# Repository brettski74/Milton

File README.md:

# Milton - The Makeshift Melt Master!

Milton is a web interface and set of utilities for controlling a solder reflow hotplate connected to various power supplies. Currently it supports bench power supplies with SCPI or Modbus support with plans to add support for other options as time, resources and information allow.

Join us on [Discord](https://discord.gg/dnQJEGFCZ9) to meet other people interested in DIY solder reflow hotplates, ask questions, make suggestions or discuss problems. You can also raise issues here and I'll take a look when I can.

Milton requires some playing around to set up and configure currently. Installation packages for Debian, Arch and a bare tarball installation should be coming soon.

## Features

* Bootstrappable - no need to hand-solder SMD components before you have a working reflow soldering solution.
* Support for SCPI and Modbus based power supplies.
* Web interface for ease of use and pretty graphs!
* Command line interface if a graphical UI is not your thing or not practical or you need to automate as part of a larger workflow.
* Real temperature control with various control algorithms available (bang-bang, feed-forward, PI and hybrid).
* Real temperature measurement without the need for an explicit temperature sensor.
* Temperature prediction models to provide noise reduction for control and to allow estimating the average temperature across your hotplate rather than for a single point that may or may not be representative of your load.
* Includes reflow profiles for tin-bismuth (SnBi) and tin-lead (SnPb) solder alloys based on JEDEC recommendations.
* Calibration via external temperature sensors if necessary to recalibrate the models for different hotplate assemblies.

## Requirements

* Linux computer with USB or RS-232 serial communications capabilities. This could include single board computers like a Raspberry PI or others.
* A variable DC power supply that supports remote control via RS-232 or USB-serial communications.
* SCPI or Modbus protocol support in your power supply.
* Perl 5 (see dependencies below)
* A [hotplate](#where-to-get-your-hotplate)

Note that power requirements depend on a lot. As a general rule, a 100mm x 100mm will need a power supply capable of 90W or more. 150W is desirable, but 90W can work reasonably well although may be a little slower - especially with heavier loads.

You will also need to match the resistance of your hotplate with your power supply. Your hotplate is basically just a copper resistor. It will dissipate whatever power you can put into it, but if the resistance is too high for your power supply's voltage capabilities or too low for it current capabilities, then you won't be able to utilize the full power output of your supply. Note that the resistance of your hotplate will increase with temperature and you generally want the highest power output at the top end of your reflow cycle. The resistance your most care about will be the resistance of the hotplate when its at your peak reflow temperature (around 220 celsius for tin-lead solder) rather than the value you measure at room temperature.

## Installation

Milton releases will come as a tarball that can be installed either as a user local installation, or as a global shared installation that can be used by multiple users. One reasons you might want to do this is if you have multiple hotplates connected to a host. One simple way of handling this is to simply run a separate instance under separate users, each with their own configuration.

You can also install the latest source by cloning the git repo and running the installation from your cloned sources. While this is the only option currently, once release tarballs start becoming available, those should be the preferred source of your installation. Release tarballs should be relatively bug free, working releases that are stable and reliable. The git repo will contain the latest code, but may include bugs and other issues from time to time.

Installation process is mostly the same. For the tarball releases, you must first extract the contents of the tarball:

```
xz -dc milton-<version>.tar.xz | tar xv
```

Now chdir to the base directory of your release (or git repo). For example:

```
cd milton-<version>
```

You should see a file called install.sh in your current directory. Run it using:

```
./install.sh
```

It should prompt your for a few things. If you are doing a global shared installation and/or using your system package manager to install perl dependencies, you may need to provide your password for sudo. If you don't trust me enough to let the installation script run sudo, then do a user local installation and use cpan or cpanm for installating your perl dependencies and it shouldn't be required. Alternatively, you can manually install all the perl dependencies and setup the required directories prior to running the installation.

The installation should get you close to a working installation, however, after installation you will still need to take care of the following tasks manually:

1. Add $MILTON_BASE/bin to your PATH environment variable.
1. Configure Milton for your power supply.
1. Calibrate your system.

### Configuring Milton

The `mledit` script can be used for editing Milton configuration files. If no filenames are specified on the command line, then it assumes you want to edit the main psc.yaml file. Filenames should be relative to the Milton configuration search path, such as controller/hybrid-pi.yaml. mledit does the following things automatically for you:

1. Find the configuration file in the Milton configuration search path.
1. If the file being edited is in the shared configuration directory, it first makes a copy in your user configuration directory and edits that.
1. Test load the file on exit to verify that it can be loaded without issue and warns you if errors are detected.

In addition to configuration basic operation of Milton, which should mostly be handled during the installation process, you will also need to [calibrate milton](CALIBRATION.md) for your particular hotplate.

## Using Milton

Before using Milton to do any real work like reflowing PCBs or testing heat sink assemblies, you will probably need to [calibrate Milton](CALIBRATION.md). Your results may vary without proper calibration of at least the RTD temperature-resistance mapping.

The command line interface uses the script `psc` to run commands. You can probably run something like:

```
psc reflow
```

to run a reflow cycle using the default reflow profile.

OR 

```
psc power --duration 900 60
```

to run the hotplate at a constant power level of 60W for 900 seconds.

TODO: Document more of the command-line options.

The web interface can be started with the command:

```
milton daemon
```

Milton is a mojolicious application that provides a web-based front end that wraps the command-line interface, so whether you run the `psc` directly or use the web interface, you're using the same code. I hope that the web interface is mostly self-explanatory, but for more advanced topics like calibration, documentation is a work in progress... or more realistically a work to be in progress. :)

### Temperature Measurement

Most temperature controlled systems use a heating element, burner or heat pump and a separate temperature sensor device. There are a lot of advantages to doing this, however some heating elements can also be used as a temperature sensor - with some caveats. This is how Milton currently works. The resistance of copper changes with temperature in a predictable and known way. In fact, this property of copper is sometimes used in a type of real, commercial/industrial temperature sensor called an RTD (Resistance Temperature Detector). These are just temperature dependent resistors made from metals such as copper or other metals/alloys with suitable properties. The copper trace on a PCB can be used as a heating element if made long and thin. If we know the resistance of the copper trace at one or more temperatures, then we can measure it's resistance to determine what its current temperature us.

Milton powers the heating element using a variable DC power supply that can be controlled via some communications interface. Currently, Milton supports SCPI and Modbus communciations over RS-232 or USB serial connections. Using this, we can read the output voltage and current. This allows us to calculate the resistance using Ohm's law. Note that there are some slight errors in these measurements due to things like lead and contact resistance, but these are negligible compared to the magnitude of the heating element resistance. They're also mostly taken care of during calibration. If we know the current temperature and the resistance of the heating element, we can use this to vary the supply voltage to send the right amount of power to get the hotplate temperature where we want it.

### Temperature Prediction

One of the drawbacks of using the heating element trace as both a heating element and a temperature sensor is that the heating element has low thermal mass and tends to vary more widely than the hotplate surface or the load on the hotplate (ie. your PCB to be reflowed). Using the heating element temperature reading directly is problematic and may be difficult to control - particularly if you're using an FR4 PCB as your hotplate. Prediction models allow us to use the measured heating element temperatures to predict what the hotplate surface temperature will be given the historical heating element temperature measurements that we've taken. With proper calibration, these models can be surprisingly accurate. The calibration provided in the release should work well for aluminimum PCBs that are assembled in a similar manner to the ones I have built. If this calibration is not working well for your particular assembly, Milton provides ways to re-calibrate the model to better reflect how your hotplate behaves.

It's also worth noting that loading the hotplate does change it's thermal behaviour.Testing so far has shown that this difference is not significant for the purpose of doing reliable solder reflow - at least with the hotplate assemblies described in this project. Feel free to experiment with new designs and let me know what you find!

If the release calibration is not working at all for you, the base predictor class - Milton::Predictor - does provide a pass-through predictor that simply gives the heating element temperature as the predicted hotplate temperature. For aluminium hotplate PCBs, this may work well enough to get you going until you can do your own calibration of the prediction model. For FR4 hotplate PCBs, this is probably not an option but if you're still using an FR4 hotplate, I highly recommend that you upgrade to aluminium. They seem to be superior in just about every way.

### Temperature Control

The control algorithms vary in their precision, need for calibration and sensitivity to mis-calibration. All of them rely on a properly calibrated temperature prediction model. Without good temperature prediction, you cannot hope to do good control. Note that raw measurements are often noisy which complicates control. You want a good prediction model for the noise filtering it provides.

There are three main control strategies currently available in Milton.

Bang-Bang control is the simplest. This works similar to the stove and oven in your kitchen. If the temperature is too low, we turn the heating element on. If the temperature is too high, we turn the heating element off - or something closely approximating off. Note that Milton always needs some current flowing through the heating element in order to measure its temperature, so the off state is really just a minimum power state. Bang-Bang control does support asymetric hysteresis, so you can specify how far above the temperature set-point the hotplate must be to turn off and how far below the temperature set-point the hotplate must be to turn on. This control strategy requires no calibration - other than a working temperature prediction model. It doesn't produce the smoothest temperature response but rather tends to oscillate around the temperature set-point by a few degrees celsius. It may also provide greater thermal and mechanical stress to your hotplate than other models due to the extreme on-off power levels that it sends into your hotplate. That said, I have not yet seen any appreciable deterioration in my aluminium hotplates after hundreds of reflow cycles and for a while this was the only control scheme I considered necessary. The results are more than adequate for solder reflow.

PI control (or PID as you may have heard it called) is a closed-loop feedback control scheme that measures the error between the desired temperature and the measured (or predicted temperature in our case) and uses that to detemine the control signal (ie. how much power to send to the hotplate) required to correct that error. The PID acronym comes from *Proportional*, *Integral* and *Differential* gains that the controller uses to produce the control signal. The proportional gain is applied to the error directly. The integral gain is applied to the integral of the error over time. The differential gain is applied to the derivative of the error over time. These three values are added together to produce the control output (ie. desired power level for the hotplate in our case). Thermal systems rarely need the differential gain or if they do use it, it's generally very small and often requires filtering of the derivative to avoid noise causing controllability problems. In our case, we simply ignore the differential term, so we really just have a PI controller with proportional and integral gains. These gains are adjustable parameters that may require some calibration, although there is a fairly wide range of values that will work reasonably well for any given hotplate. There are algorithms for calibrating these parameters - such as the well-known Ziegler-Nichols method, which Milton does not currently implement. Milton does have a calibration routine for the PI gains based on temperature prediction and a least-squared-error optimization, but the results so far were not impressive and so far the results with educated guesses have been better than what the optimization provided. The proportional gain generally gets the control into the ballpark, but with some offset error. The integral gain slowly corrects for this offset error, which brings the system closer to the desired state over time. PI controllers are good at adjusting to changing environmental conditions (eg. a load on the hotplate) but can also be prone to overshoot or undershoot when there are control changes required (eg. different rates of heating required). Proper selection of the gain values can improve this.

Feed-forward control requires a model for how the system responds to control inputs and then uses this model to estimate how much power is required to get from the current system state to the desired system state. It is the most sensitive to miscalibration, but when well-calibrated can often produce the smoothest, over/undershoot free temperature response you're likely to see. The downside is that feed-forward control is not great at adjusting for changes in environmental conditions like the PI controller. Feed-forward will generate higher power output commands in response to a load on the hotplate, but is unable to correct for the offset error that results. For most practical loads, this offset error is unlikely to be large enough to prevent reliable reflow, but a PCB loaded with components with high thermal mass may produce lower temperatures and/or require longer dwell time. This is why the feed-forward controller is implemented as a hybrid controller with the PI controller - HybridPI - so you can combine the best of both worlds. 

## Building Milton

TODO

## Where To Get Your Hotplate?

In theory, virtually any hotplate with a copper heating element should work but it was designed with PCB hotplates in mind. There are some example layouts for aluminium PCBs available in the [resources](resources) directory. You can also roll your own or get help from [Emmett](https://github.com/brettski74/Emmett) to build one to meet your needs.

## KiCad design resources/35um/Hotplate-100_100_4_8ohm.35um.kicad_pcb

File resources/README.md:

# Milton Resources

Here you'll find a collection of resources for setting up hotplates and other hardware to work with Milton.

## Safety

You'll probably see safety mentioned more than once in this repo. A reflow hotplate is a potentially
dangerous device that could cause serious burns or pose a fire hazard if not built, maintained and used
carefully. Commercial devices in many markets are required to go through extensive testing to ensure that
they are inherently safe and mitigate most of the common fire and burn hazards. I am not an expert. I'm
just a guy on the internet giving you my best opinions about how I think you can mitigate some of these
risks. Ultimately, if you choose to build a solder reflow hotplate using mine or anyone else's designs,
you understand that you are responsible for ensuring that the device that you build is safe and operated
safely. While I have included advice on how I think some of these risks can be mitigated, it is entirely
possible that you follow everything I say to perfection and you could still burn yourself, others or your
house.

### Thermal Fuse

The thermal fuse is a soldered link incorporated into the heating element circuit that must be in place
for the heating element to work. Pay close attention to the setup instructions that describe how to set
up the thermal fuse if you want it to work reliably. The type of solder used as well as the size and
geometry of the link and the pads on which it is mounted factor into how reliably it *trips* at the
expected temperature. Under normal use, this component should never make a difference, but in the event of
a thermal fault, it provides a last line of defence that will prevent the hotplate from continuing to heat
past a useful limit. If set up well, the link should drop at or below about 240°C. An incorrectly set up
thermal fuse link may stay connected well above 280°C or higher. There are some common household materials
that can ignite at these temperatures.

### Power Connections

The recommended method of connecting power to the board involves using solid copper wire and screw terminals
to securely clamp the wire in place. Solid copper wire is used for its rigidity. In the event of a thermal
fault, the hotplate could potentially get hot enough to reflow the power connection solder joints. If floppy,
flexible wires have been used, these wires may drop away from the board and fall... who knows where? The
intention of using solid copper wire is that they are bent into shape so the wires are under neglible stress
and the screw terminals hold them firmly in place so that if the power connections reflow, the power connection
wires stay put and don't inadvertently fall onto anything which might create a hazard or other problem.

You may get the idea that the power connections themselves could be used as a safety device and disconnect
power during a thermal fault, however, this is not recommended for at least the following reasons.

1. Copper doesn't make a good spring and even if you can create sufficient strain in the wires during setup
to make them spring away to a safe position if the joints reflow, copper does not retain that strain well
and it will relax over the kinds of temperatures that the power connections may be exposed to. After some
number of reflow cycles, that strain may be all but gone and then the wires won't move much or at all in a
subsequent thermal fault.
1. Materials that are good at being springs and are likely to retain that springiness as the hotplate goes
through many reflow cycles (eg. Phosphor Bronze) have other challenges such as poor electrical conductivity
and poor solderability due to surface oxidation that may make them difficult to form high quality joints
with the hotplate PCB.
1. Even with a good spring material like phosphor bronze and a good solution for the conductivity and
solderability problems, the spring may still relax over time due to thermal cycling, so if this was to
be your primary safety device, you'd need to do periodic maintenance to check the spring strain and make
sure it's still sufficient and still moves the power connections to a safe position after some period of
time or number of reflow cycles (eg. maybe once per year or 100 reflow cycles)

Note that none of the above should be taken as a recommendation or advice on how to do this. I don't
recommend it and wanted to share some of my thought process as to why. If you decide to try to design
something like this, I'd love to hear how you go but that's your mission, not mine.

## Hotplate Layouts

A collection of off-the-shelf hotplate PCB layouts that should work well with Milton. There should be an
option here that should work for many common power supply specifications. See the table below for which
layout is recommended for your particular power supply. These were all generated using [Emmett](https://github.com/brettski74/Emmett),
so if none of these suit your needs, you can use Emmett to help design a layout that does.

Ideally, you want your hotplate to have maximum power available near the peak reflow temperatures. This is
assumed to be around 220°C, which is the typical peak reflow temperature for standard tin-lead solders. Since
the resistance of the heating element increases with temperature, this means that we want to design to achieve
the desired power into your hotplate when the heating element is hot. This does mean that for many power supplies
you may find that you are current-constrained at low temperatures and cannot achieve the design power, but this
is usually not necessary at lower temperatures. Worst case, for a severely limited power supply (eg. a 30V 3A supply)
you may find that it cannot keep up with the initial preheat ramp but that it catches up during the soak stage.
There is also the *slow-power* reflow which lengthens the time for each stage to allow for more power limited
setups to still follow a reasonable profile and get good results.

### Track Thickness

A 1 ounce copper layer *should* be 35 microns thick, so the *standard* calculations use this value for estimating
the resistance of the finished PCB. In practice, some manufacturers seem to produce slightly higher resistance
than the physics would predict. There are various possible explanations for this, including thinner than expected
copper layer, narrower than expected traces, impurities in the deposited copper and potentially more. Remember
that the PCB manufacturers are in the business of making circuit boards, not large, flat resistors to any degree
of precision. We use the track thickness parameter in [Emmett](https://github.com/brettski74/Emmett) to adjust for
observed manufacturing variances, but these may change over time. Therefore, it is entirely possible that you may
order a PCB using a particular layout and when the boards arrive, the resistance of the heating elements on those
boards is significantly different than expected. If your power supply has a lot of headroom, then it's usually not
a big deal, but if you're working within some tight power constraints such as a 30V 3A supply, it may present a
problem with getting the expected performance.

I've used two different manufacturers for aluminium hotplate PCBs - JLCPCB and PCBWay. I'm not sponsored by either
of them, they're just the ones I've used because I'm cheap and so are they. JLCPCB boards seems to come back with
resistances that are more consistent with a 29 micron thick copper layer, so if you're planning to order from JLCPCB
use the layouts in the 29um directory. PCBWay seems to be more consistent with a 35 micron copper layer, so use the
35um directory if you're ordering from PCBWay. For any other manufacturers, I'd suggest starting with the 35um
layouts and see what you get. Also let me know how they are and I can add details here for the benefit of others.

### Hotplate Layout Recommendations

|Power Supply Description|Max Voltage|Max Current|Max Power|Recommended Hot Resistance|Examples|
|---|---|---|---|---|---|
|30V 3A Bench Supply|30V|3A|90W|10Ω|RD DPS3003, ELV DPS5315, etc|
|USB-PD Supply|20V|5A|100W|4Ω|Includes FNIRSI DPS-150|
|30V 5A Bench Supply|30V|5A|150W|6Ω|RD DPS3005, many others|
|Higher Voltage Bench Supply|40+V|5A|150+W|10Ω|RD DPS5005, DPS5015, DPS5020, etc|

### Open Loop Suggestions

Note that even if you don't have a power supply that can be remotely controlled and is compatible with Milton,
there are still some reasonably safe ways to do DIY solder reflow without any control at all. This is also an
approach you can use for bootstrapping your setup if you don't have a supported power supply and want to build
a custom hotplate controller board. **NOTE THAT THIS DOES ENTAIL SOME ADDITIONAL RISK** - especially if using a
hotplate without any safety device built in like a thermal fuse. Note that I wouldn't recommend the open loop
approach for things like rework or preheat, because these operations lack a clear indicator of temperature. If
you want to use your hotplate for those tasks, you really need temperature control in my opinion.

A 100mmx100mm aluminium hotplate mounted on metal standoffs or similar will require about 85W to hold the
temperature steady at 220°C (428°F). All of the following discussion assumes a 100mm x 100mm aluminium PCB
hotplate mounted in a manner similar to those in my assembly instructions. If these assumptions do not apply,
the calculations may be wildly wrong which could lead to disappointment either due to reflow never happening
or due to your house being consumed in a fiery blaze.

If you're going to use a PCB hotplate for solder reflow without temperature
control, the key is to limit the available power at peak temperatures and to watch for evidence of reflow to 
know when the process is done and you should shut off the power. There are two main ways to limit the power
available at peak temperature. One is by selection of a hotplate resistance that is suitable for your power
supply. This option is available to anyone. The other is by controlling the voltage and/or current available 
to the hotplate. This option depends on whether your power supply has adjustable limits for its output.

The basic process for open loop reflow is this:

1. Apply solder paste and place your components on your PCB.
2. Place the PCB on the hotplate
3. Set the correct voltage and current limits - if applicable.
4. Turn on the power and watch.
5. When you see the solder paste change from dull grey paste into silvery molten metal, wait for 10-15 seconds
after you see **all** solder joints have reflowed, then turn off the power.
6. Allow the board to cool in place on the hotplate for about 10 minutes before removing it.

Note that the procedure is dependent on your being able to see evidence of reflow occurring. If you will not
be able to observe the solder reflow for any reason, this approach is not advisable.

Consider the following plot.  These were done with a hotplate PCB that has a resistance of about 10Ω at 220°C.
It's an ideal resistance for a 30V, 3A power supply with constant voltage and constant current limiting
typical of some budget priced and lower power benchtop power supplies. These plots were created using this
hotplate PCB and the power supply limited to 30V and 3A to simulate such a power supply. Maximum power
available is 90W. With this supply doing no temperature control, just keep the voltage and current within
limits, we were able to hit 220°C in about 240 seconds. This is a reasonable rate of heating for an open
loop reflow hotplate. It's not ideal, but the rate of heating is not too high, to allow the load to heat
up relatively evenly. The rate should be fast enough that you can reflow before burning off all of the flux -
at least good enough for the home hobbyist.

If you have a hotplate with a different resistance, then you can
calculate a voltage and current that should produce a similar result for your specific hotplate. Determine
it's resistance at peak reflow temperature. If you don't know that value, measure the resistance at room temperature. Let's say
that it's 25°C in your room and you measure the resistance of your hotplate as 4Ω. You first calculate it's
resistance at $T_{0} = 20°C$. Note that the temperature coefficient of resistance for copper is 0.00393.

$$ R_{0} = \frac{R}{1 + \alpha \lparen T - T_{0} \rparen } = \frac{4}{1 + 0.00393 \lparen 25 - 20 \rparen } $$

$$ R_{0} = \frac{4}{1 + 0.00393 \times 5} = \frac{4}{1.01965} = 3.923 \Omega $$

Next calculate the resistance at your chosen peak temperature - let's say 210°C. It's a good idea to aim for a
slightly lower peak temperature to give yourself extra safety margin since you don't have the benefit of
temperature control to keep the temperature from exceeding safety limits, so aiming for something like 200°C
or 210°C is more prudent.

$$ R_{peak} = R_{0} \lparen 1 + \alpha \lparen T - T_{0} \rparen \rparen $$

$$ R_{peak} = 3.923 \lparen 1 + 0.00393 \lparen 210 - 20 \rparen \rparen $$

$$ R_{peak} = 3.923 \lparen 1 + 0.00393 \times 190 \rparen $$

$$ R_{peak} = 3.923 \times 1.7467 = 6.852 \Omega $$

Next calculate the voltage required to sink 90W into $R_{peak}$.

$$ V_{max} = \sqrt{P R_{peak}} = \sqrt{90 \times 6.852} = \sqrt{616.68} = 24.8V $$

Finally, calculate the current that would be required to sink 90W into $R_{peak}$.

$$ I_{max} = \sqrt{ \frac{P}{R_{peak}} } = \sqrt{ \frac{90}{6.852} } = \sqrt{ 13.135 } = 3.624A $$

Set your voltage limit to $V_{max}$ and your current limit to $I_{max}$, hook up your hotplate and turn it on.

This assumes that you have a power supply that does both voltage limiting and current limiting and that these
limits can also be adjusted. This is also often referred to as constant-current/constant voltage (CCCV) modes
of operation. Realistically, open loop reflow is probably only realistic on these kinds of power supplies. A
fixed output supply with no current limiting is probably inappropriate and would need some additional electronics
to effectively and safely drive the hotplate. Technically it's possible, but there are some challenges and
potential risks that, in my humble opinion, are not worth it.

It's worth noting once again that **THERE IS SOME ADDED RISK IN OPEN LOOP SOLDER REFLOW**. Absolutely do not
let the hotplate run unsupervised and shut off the power at the first sign of anything going awry.

## Bending Jig

To build a reliable thermal fuse, you need to bend some 10AWG or 6mm² copper wire into a U shape with dimensions
to land on a couple of relatively small pads. I've designed a small jig that you can 3D print that allows you to
bend these accurately and repeatably. It includes a length gauge on the side so you can cut the exact length of
wire required and a hole and groove in the top that you can use for bending the two ends. Due to a small amount
of relaxation in the metal after bending, you may have to tweak it slightly with pliers once you're done, but
that's fairly straightforward to do after the jig has done most of the work. The jig is available both as an STL
file and as the original OpenSCAD source that I used to create it.

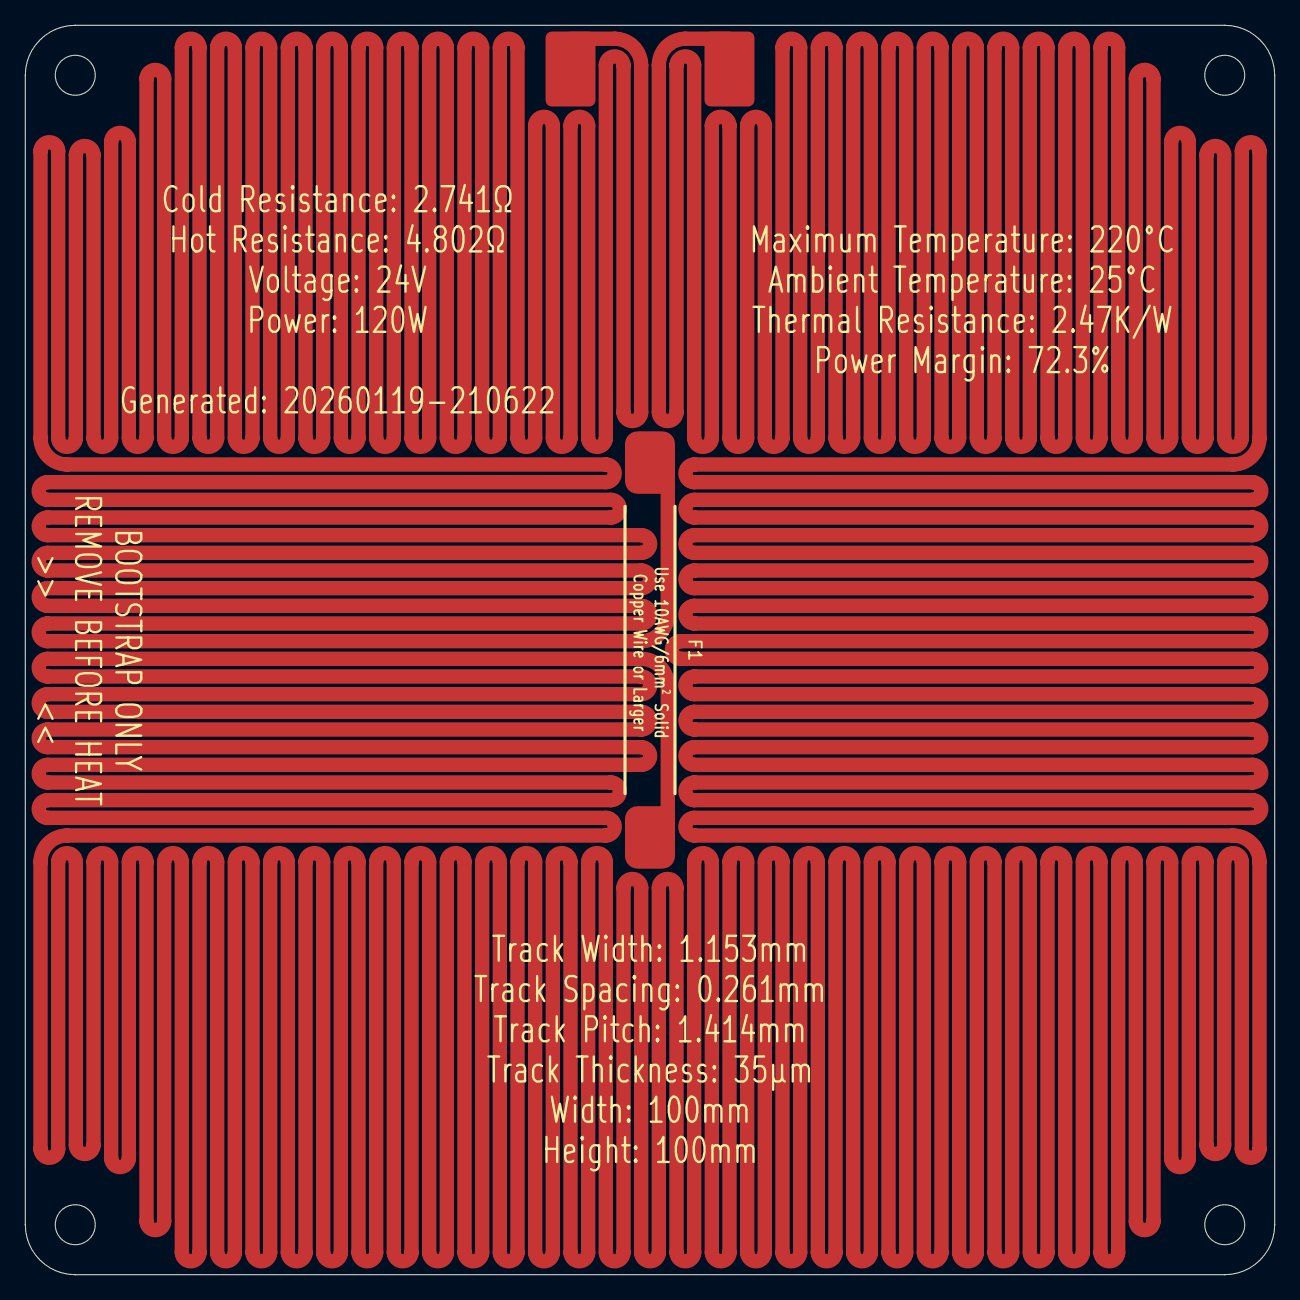
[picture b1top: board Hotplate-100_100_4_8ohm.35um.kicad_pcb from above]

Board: 2 copper layers, 100.0 x 100.0 mm, 3 parts (0 on the bottom side), 2 nets.

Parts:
F1: Thermal Fuse, SN100C, Front, 35mm
J1, J2: Hotplate_Power_Connection; SMD_PowerConnection_4x6mm

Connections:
unnamed: F1.1, J1.1
unnamed: F1.2, J2.1

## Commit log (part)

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2025-06-19 First few tests of the Config module.
2025-06-19 Final set of tests for include functionality added.
2025-06-19 Fixed test yaml files location to /t rather than /t/test
2025-06-19 Fixed Cursor's screwing with controller.yaml yet again!
2025-06-20 Working version of DPS interface that can get/set voltage and current.
2025-06-22 Added tests for HP/PiecewiseLinear.pm
2025-06-22 Implemented prediction methods in ThermalModel with unit tests.
2025-06-22 Made estimateFromPoints method "private".
2025-06-22 Added start and end methods to PiecewiseLinear.pm
2025-06-22 Checkpoint commit during EventLoop and calibrate command initial development.
2025-06-23 Bug fixes to get a command that executes - not working, but executes now.
2025-06-24 Many bug fixes and improvements like nested hash support in HP::DataLogger.
2025-06-26 Added tests for the merge method - as yet unimplemented.
2025-06-26 Added getPoints method to PieceWiseLinear to make a more sanctioned and safe way to access the internal state.
2025-06-26 Added merge method to HP::Config.
2025-06-26 Modified PieceWiseLinear tests to use getPoints to pull out internal state for inspection.
2025-06-26 Added configFileExists method to HP::Config
2025-06-26 Fixed minor syntax errors in calibrate.pm
2025-06-26 Added basic coding style guidelines.
2025-06-26 Added bare return requirements.
2025-06-26 Added _time and _now methods to EventLoop class to facilitate more testing.
2025-06-27 Added additional defaulting case for reset threshold for SteadyStateDetector.
2025-06-27 Fixed options method return type.
2025-06-30 Added mean_square_error subroutine.
2025-07-01 Added quick and dirty power command to send constant power to the power supply.
2025-07-01 Added tests to ensure that status object is correctly built for key events.
2025-07-02 Naming convention fix.
2025-07-02 Added support for commands to add additional columns for logging in their configuration.
2025-07-02 Added tests to ensure that the event-loop object is included in the status hash.
2025-07-02 Checkpoint commit prior to renaming main module namespace.
2025-07-02 Added support for named segments in PiecewiseLinear class.
2025-07-03 Refactored methods for setting temperature calibration on the RTDController class to be more specifically about temperature, to allow adding thermal resistance and heat capacity calibrations as well.
2025-07-03 Modified configuration file search path.
2025-07-04 Added PowerSupplyControl::Command::replaceFile method. Refactored timestamp into ValueUtils module.
2025-07-04 Fixed order of command constructor parameters.
2025-07-05 Initial commit of hccal command - untested.
2025-07-05 Renamed calibration commands to use same naming pattern.
2025-07-07 Added the addHashPoints method.
2025-07-07 Added fan support methods in EventLoop.
2025-07-09 rtcal command improvements. More stable/reliable now.
2025-07-11 Initial commit of refactored PowerSupplyControl::Interface class. No unit tests, yet. No refactoring of dependent code, yet. Many things are probably broken by these changes.
2025-07-12 Added support for external temperature measuring devices in RTDController.pm
2025-07-12 Also commit RTDController tests!
2025-07-12 Added test cases for setPower when last polled current is zero.
2025-07-12 Added code for external temperature sensing devices.
2025-07-13 Updated Interface.pm to only call _setVoltage and _setCurrent when changes are significant to avoid unnecessary blocking comms inside the event loop.
2025-07-13 Made the default implementation for voltage and current precision configurable to support a wide range of devices.
2025-07-15 Checkpoint commit.
2025-07-17 Removed ReplayInterface. Not used and effective obviated by the reprocess command.
2025-07-19 Added support for asymmetric hysteresis in BangBang.
2025-07-19 Fixed broken tests.
2025-07-19 Added cut-off-temperature to BangBang configuration.
2025-07-19 Added WebDataLogger to prepare for streaming to the Web UI.
2025-07-19 More changes for webui messaging support.
2025-07-20 Checkpoint commit of this steaming pile of AI generated poo before I start the oh-so-fun task of untangling this mess into something that actually works as opposed to just looking pretty but otherwis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
2025-07-22 Checkpoint before we try my new nonlinear IIR filter prediction model.
2025-07-23 Renamed web_server.pl to psc_web.pl to avoid possible name clashes with overly generic name.
2025-07-25 Fixed tests so that they run with make test.
2025-08-02 It's been a while...
2025-08-02 Added missing test data.
2025-08-02 Added reset, setTau and setPeriod methods to LowPassFilter.
2025-08-03 Clean up minimumSearch and minimumSearch2D along with reliable tests.
2025-08-03 Refactoring for generalized minimumSearch.
2025-08-04 TwoStageBackPredictor calibration seems to be working - but suggests some simplifications may be in order.
2025-08-05 Added multi-processing capability to minimumSearch.
2025-08-09 Updated available commands to reflect current requirements for reflow operations.
2025-08-09 Added Milton logo image.
2025-08-26 Added ability to identify the path of the file from which configuration was included in a config file, not just the main config file.
2025-08-26 Committed missing test file.
2025-08-28 Hide external temperature dataset if it's not available.
2025-08-28 Clamp the integral if it's too big.
2025-08-30 Start of renaming of the code packages for the Milton name.
2025-09-01 Updated description for BandedLPF predictor and HybridPI controller.
2025-09-02 Initial README file added.
2025-09-02 Fixed getPowerLimited tests based on the separation of limits and cutoff.
2025-09-03 Add POD documentation to Milton::Predictor::LossyLPF
2025-09-03 Added POD documentation for BandedLPF.
2025-09-07 Updated PiecewiseLinear to allow multiple attributes per segment, ability to specify limits and cutoff disablement in profiles and provided a new fuse-test profile.
2025-09-14 Added design and STL files for thermal fuse bending jig.
2025-09-15 Added README.md to resources directory.
2025-09-15 Update HotplateSetup.md
    Fixed ordering of creation of stand for thermal fuse link in setup instructions.
2025-09-15 Image disclaimer regarding damaged board in hotplate setup images.
2025-09-16 Added note about pre-release status to README.
2025-09-21 Fixes #2 calls heating element prediction during tuning cycles.
2025-09-21 Cleaned up separation between reflow and setup commands in webui.
2025-10-15 Added 160x120mm 35um layout.
2025-11-17 More typo fixes in README.md.
2025-11-26 Initial implementation of rth command.
2025-12-01 Improved steady state prediction. Added mass compensation for rth command.
2025-12-16 Fix typos in resources/README.md
2025-12-21 Added bootstrap.sh script to help with initial setup.
2025-12-21 Detecting perl modules installation methods.
2025-12-21 Checkpoint.
2025-12-24 Standard make configurationtemplates added.
2025-12-24 Include install-config in setup script.
2025-12-24 Update webui paths to use Milton base directory.
2025-12-24 Update BlueToothCtl class to handle different bluetoothctl versions.
2025-12-28 Added reallyclean target to Makefile.
2025-12-28 Modified config search paths to use $MILTON_BASE environment variable.
2025-12-29 Make the hybrid-pi-gains.yaml file optional.
2025-12-29 DataLogger attempts to create the log directory if it doesn't exist.
2025-12-29 Suggest corrective action if port permissions need adjustment.
2025-12-29 Add Carp import to Milton::Config::Utils.
2025-12-29 Updated Makefiles to set PERL5LIB and ensure successful installation or perl scripts and modules.
2025-12-29 Added help target to child Makefiles.
2025-12-30 Moved fan configuration out of the default psc.yaml into an optional file. Added a warning message to also output the first automatic RTD calibration point - the one that's actually measured!
2025-12-30 Fixed BASEDIR in some Makefiles so that the common rules for perl scripts work as expected.
2025-12-30 Replaced obsolete 25mm thermal fuse footprint with new 35mm thermal fuse footprint.
2025-12-30 Updated SCPI interface configurations to include metadata to help with SCPIScanner.
2025-12-31 mledit ensures target directory exists for new files.
2025-12-31 Improved warning messages during device scans. Make blank $id response clearer and include the device name in the message to the user.
2025-12-31 Warning wording only.
2025-12-31 Switched to sysread/syswrite for USBTMC interface. Seems to be more reliable.
2026-01-01 Refactoring of the logger framework to support efficient debug output.
2026-01-01 Debug updates.
2026-01-01 Updated unit tests for Config to use Path::Tiny and fix broken tests.
2026-01-02 Initial working version of SCPIScanner for SCPI-Serial devices.
2026-01-02 Added working SCPI scan for USBTMC instruments.
2026-01-03 Added interface setup to the milton-setup script.
2026-01-03 Set MILTON_BASE environment variable in milton-setup.
2026-01-03 Minor fix in MILTON_BASE setting in .miltonenv
2026-01-03 Fixed parameter name in milton-setup.pl.
2026-01-03 Fixed variable name in select_power_supply_model in milton-setup.pl.
2026-01-03 Fixed SCPIScanner command length detection bugs from manual testing of milton-setup.
2026-01-04 Fixed bug in find_config_files_by_path where the document reference was incorrect.
2026-01-04 Ensure that shutdown commands in shared configuration files are sent to the power supply on disconnect during the scan.
2026-01-05 Moved shared vs local installation detection from milton-setup to install.sh.
2026-01-05 Fixed typo in milton-setup.pl.
2026-01-05 milton-setup improvements. Added fatal error on failure to install dependencies, plus troubleshooting information. Added ability to change ownership of the installation for shared installations.
2026-01-06 Minor updates to CALIBRATION.md and README.md.
2026-01-07 Minor update to HotplateSetup.md.
2026-01-09 Increased flexibility of SCPICommon - command strings must now include the separator if required, allowing for command strings with no trailing whitespace separator.
2026-01-09 Updated SCPICommon to support separate voltage and current measurement commands.
2026-01-09 Rewrote dependency checks to properly detect installation after trying last installation method.
2026-01-09 Minor bugfixes in milton-setup.pl and install.sh
2026-01-09 Offer to create users and groups that don't exist.
2026-01-09 Dereference symbolic links in chown command.
2026-01-09 Default to the first detected power supply if one was found, otherwise 'S' for "Select"
2026-01-09 Include -L in chown command to traverse symbolic links to directories.
2026-01-09 Second attempt at fixing IO::Pty dependency problem.
2026-01-10 Add profile parameter to linear command from the web UI.
2026-01-10 Added initial tests for linear reflow command.
2026-01-10 Debug output now includes filename and line number of the caller.
2026-01-11 Added linear reflow tuning plus numerous linear reflow bug fixes.
2026-01-11 Don't trim if we're tuning in linear reflow command.
2026-01-12 More PR bug fixes.
2026-01-12 Project settings updates.
2026-01-19 Moved old PCB layouts to legacy directory to make way for new bootstrappable layouts.
2026-01-21 Updated bootstrap jumper to not straddle multiple nets and include a solder mask dam between the jumper pads.
2026-01-27 Cleaned up some debug output and unused imports.
2026-01-29 Lowered startup current default to 100mA to avoid undesirable heating of the hotplate during calibration on slow responding power supplies.
2026-02-01 Add extra layer of directory depth support in Makefile
2026-02-01 Implemented polling option for multimeter temperature reads.
